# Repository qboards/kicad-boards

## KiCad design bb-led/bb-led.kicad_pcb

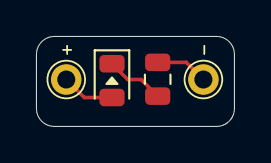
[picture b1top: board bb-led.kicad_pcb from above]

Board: 2 copper layers, 11.0 x 5.0 mm, 5 parts (1 on the bottom side), 3 nets.

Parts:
BB-LED: LOGO_BRD_REF; logo-3mm
D1: LED; LED_0805_2012Metric
J1, J2: Conn_01x01_Male; PinHeader_1x01_P2.54mm_Vertical
R1: R; R_0805_2012Metric

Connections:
unnamed: D1.1, R1.1
unnamed: D1.2, J1.1
unnamed: J2.1, R1.2

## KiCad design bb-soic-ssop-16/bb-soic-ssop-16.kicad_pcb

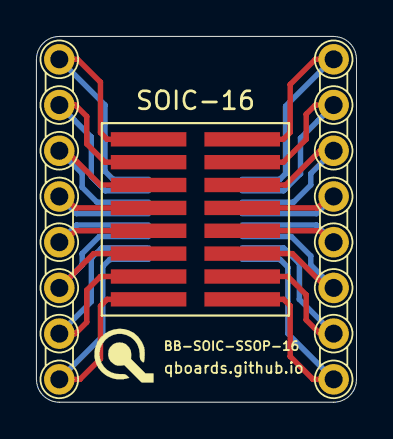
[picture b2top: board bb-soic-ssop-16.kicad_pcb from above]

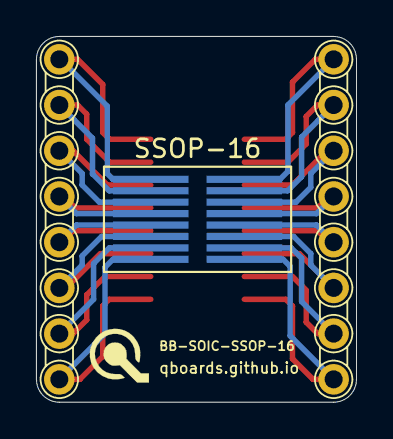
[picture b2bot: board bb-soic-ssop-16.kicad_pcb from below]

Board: 2 copper layers, 17.8 x 20.3 mm, 6 parts (2 on the bottom side), 16 nets.

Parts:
BB-SOIC-SSOP-16, BB-SOIC-SSOP-16#2: LOGO_BRD_REF; logo_url-3mm
J1, J2: Conn_01x08_Male; PinHeader_1x08_P2.54mm_Vertical_dual
SOIC-16: IC-16; SOIC-16
SSOP-16: IC-16; SSOP-16

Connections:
unnamed: J1.1, SOIC-16.1, SSOP-16.8
unnamed: J1.2, SOIC-16.2, SSOP-16.7
unnamed: J1.3, SOIC-16.3, SSOP-16.6
unnamed: J1.4, SOIC-16.4, SSOP-16.5
unnamed: J1.5, SOIC-16.5, SSOP-16.4
unnamed: J1.6, SOIC-16.6, SSOP-16.3
unnamed: J1.7, SOIC-16.7, SSOP-16.2
unnamed: J1.8, SOIC-16.8, SSOP-16.1
unnamed: J2.1, SOIC-16.9, SSOP-16.16
unnamed: J2.2, SOIC-16.10, SSOP-16.15
unnamed: J2.3, SOIC-16.11, SSOP-16.14
unnamed: J2.4, SOIC-16.12, SSOP-16.13
unnamed: J2.5, SOIC-16.13, SSOP-16.12
unnamed: J2.6, SOIC-16.14, SSOP-16.11
unnamed: J2.7, SOIC-16.15, SSOP-16.10
unnamed: J2.8, SOIC-16.16, SSOP-16.9

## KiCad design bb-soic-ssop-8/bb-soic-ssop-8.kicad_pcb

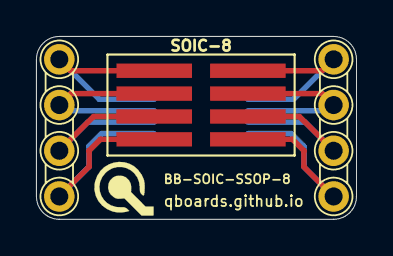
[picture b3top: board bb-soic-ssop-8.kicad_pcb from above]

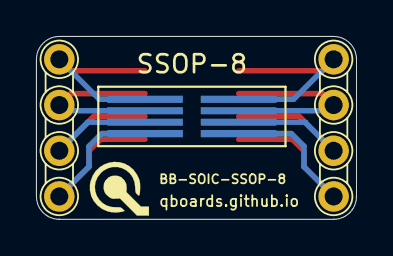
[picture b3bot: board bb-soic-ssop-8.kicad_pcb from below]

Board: 2 copper layers, 17.8 x 10.2 mm, 6 parts (2 on the bottom side), 8 nets.

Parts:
BB-SOIC-SSOP-8, BB-SOIC-SSOP-8#2: LOGO_BRD_REF; logo_url-3mm
J1, J2: Conn_01x04_Male; PinHeader_1x04_P2.54mm_Vertical_dual
SOIC-8: IC-8; SOIC-8
SSOP-8: IC-8; SSOP-8

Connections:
unnamed: J1.1, SOIC-8.1, SSOP-8.4
unnamed: J1.2, SOIC-8.2, SSOP-8.3
unnamed: J1.3, SOIC-8.3, SSOP-8.2
unnamed: J1.4, SOIC-8.4, SSOP-8.1
unnamed: J2.1, SOIC-8.5, SSOP-8.8
unnamed: J2.2, SOIC-8.6, SSOP-8.7
unnamed: J2.3, SOIC-8.7, SSOP-8.6
unnamed: J2.4, SOIC-8.8, SSOP-8.5

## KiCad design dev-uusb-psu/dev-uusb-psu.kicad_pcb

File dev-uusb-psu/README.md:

# QBoard DEV_UUSBPSU

Small 3.3V/5V breadboard power supply with microUSB connector

# Downloads

* [Gerbers](output/gerbers.zip)
* [Schematic](output/schematic.pdf)

# About QBoards

See [here](https://github.com/qboards/kicad-boards#about-qboards)

# Licensing

See [here](https://github.com/qboards/kicad-boards#licensing)

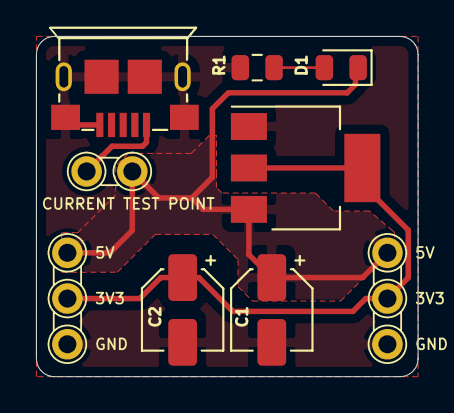
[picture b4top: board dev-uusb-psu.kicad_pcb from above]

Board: 2 copper layers, 21.2 x 18.9 mm, 9 parts (0 on the bottom side), 5 nets.

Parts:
C1, C2: 10uF; CP_Elec_4x3
CURRENT TEST POINT: Conn_01x02_Male; PinHeader_1x02_P2.54mm_Vertical
D1: SMD-LED-CLEAR-GREEN_0805_; LED_0805_2012Metric
J1, J2: Conn_01x03_Male; PinHeader_1x03_P2.54mm_Vertical
R1: 150; R_0805_2012Metric
USB1: MICRO-USB-SMD-B-_10118193-0001LF_; MICRO-USB5+6P-SMD-0.65-B
VREG1: LM1117-3.3; SOT-223-3_TabPin2

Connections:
+3V3: C2.1, J1.2, J2.2, VREG1.2
+5V: C1.1, CURRENT TEST POINT.1, D1.1, J1.1, J2.1, VREG1.3
GND: C1.2, C2.2, J1.3, J2.3, R1.2, USB1.5, USB1.6, USB1.7, USB1.8, USB1.9, USB1.10, USB1.11, VREG1.1
unnamed: D1.2, R1.1
unnamed: CURRENT TEST POINT.2, USB1.1
